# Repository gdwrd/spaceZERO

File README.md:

# spaceZERO
spaceZERO - A 48-key ortholinear keyboard

README.md will be updated soon

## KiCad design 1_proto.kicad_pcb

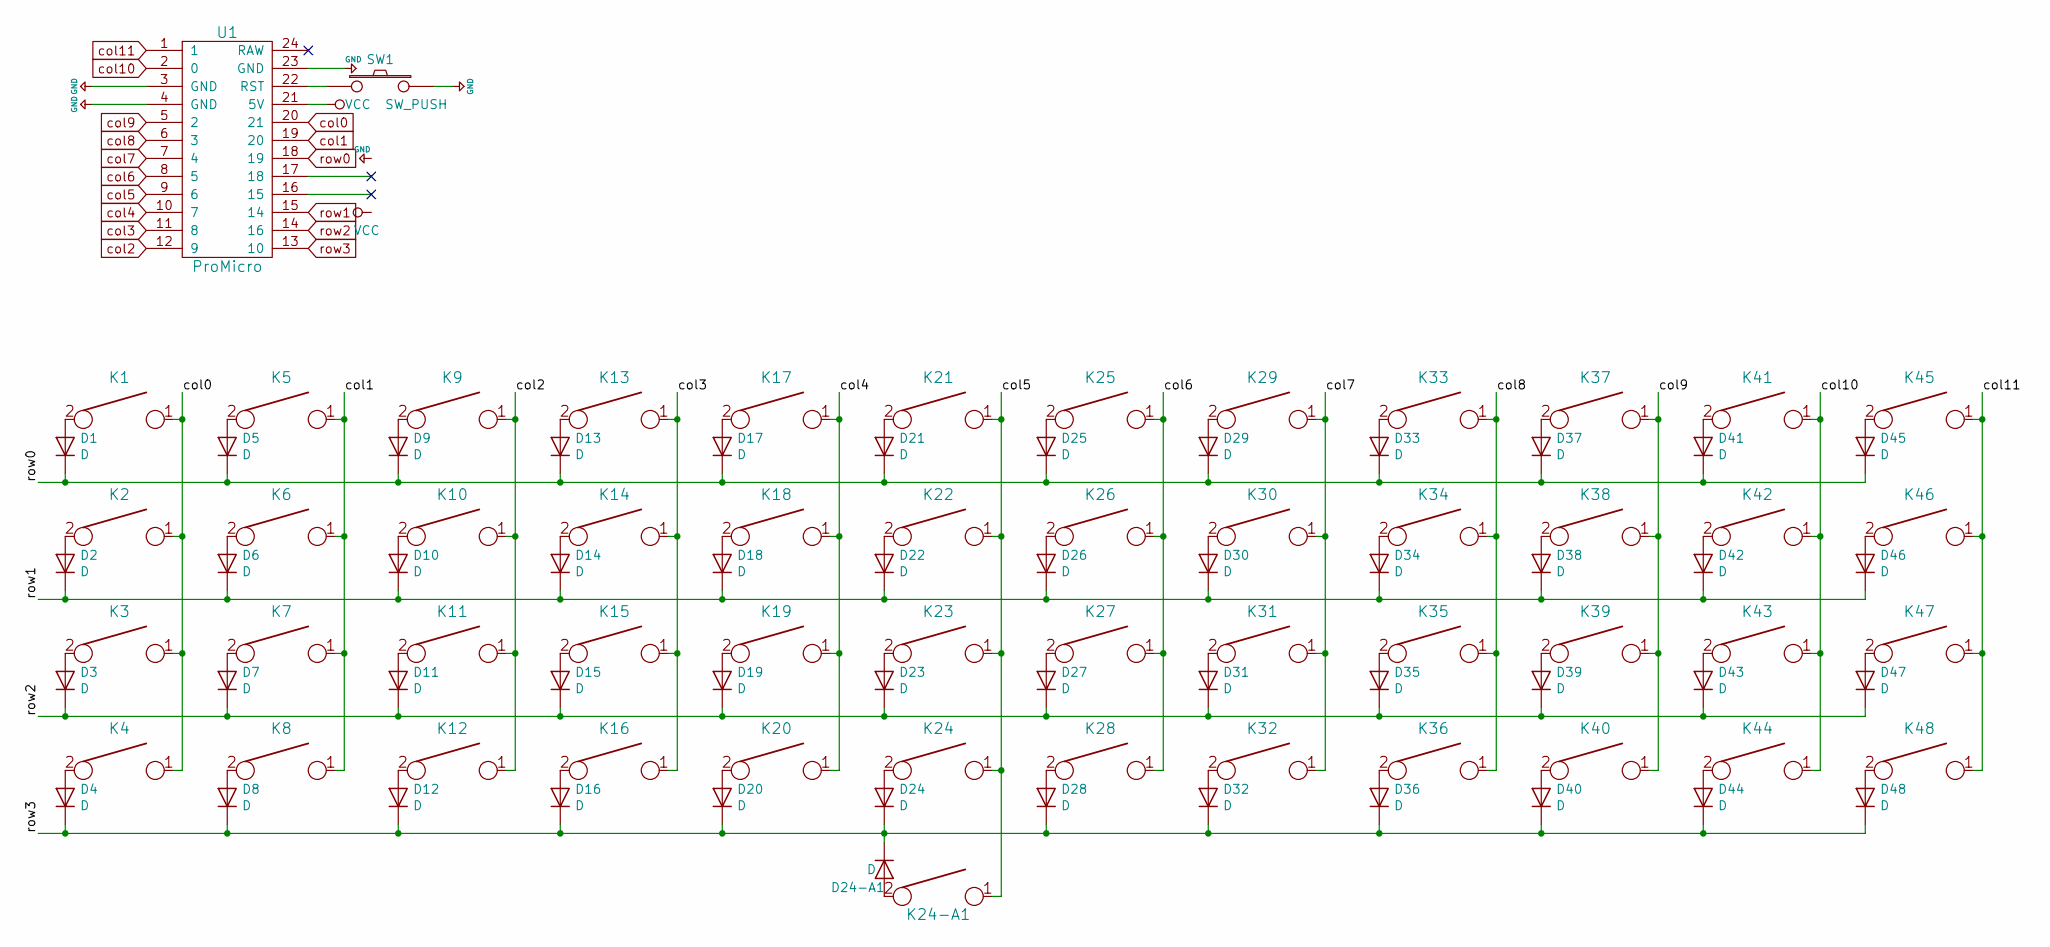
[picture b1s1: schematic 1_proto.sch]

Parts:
D1, D2, D3, D4, D5, D6, D7, D8, D9, D10, D11, D12, D13, D14, D15, D16, D17, D18, D19, D20, D21, D22, D23, D24, D24-A1, D25, D26, D27, D28, D29, D30, D31, D32, D33, D34, D35, D36, D37, D38, D39, D40, D41, D42, D43, D44, D45, D46, D47, D48: D; D_SOD123_axial
K1, K2, K3, K4, K5, K6, K7, K8, K9, K10, K11, K12, K13, K14, K15, K16, K17, K18, K19, K20, K21, K22, K23, K24, K24-A1, K25, K26, K27, K28, K29, K30, K31, K32, K33, K34, K35, K36, K37, K38, K39, K40, K41, K42, K43, K44, K45, K46, K47, K48: KEYSW; Mx_Alps_100
SW1: SW_PUSH; SW_PUSH_6mm
U1: ProMicro; Pro_Micro

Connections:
+5V: SW1.2, U1.3 (GND), U1.4 (GND), U1.23 (GND)
unnamed: D1.2 (A), K1.2
unnamed: D2.2 (A), K2.2
unnamed: D3.2 (A), K3.2
unnamed: D4.2 (A), K4.2
unnamed: D5.2 (A), K5.2
unnamed: D6.2 (A), K6.2
unnamed: D7.2 (A), K7.2
unnamed: D8.2 (A), K8.2
unnamed: D9.2 (A), K9.2
unnamed: D10.2 (A), K10.2
unnamed: D11.2 (A), K11.2
unnamed: D12.2 (A), K12.2
unnamed: D13.2 (A), K13.2
unnamed: D14.2 (A), K14.2
unnamed: D15.2 (A), K15.2
unnamed: D16.2 (A), K16.2
unnamed: D17.2 (A), K17.2
unnamed: D18.2 (A), K18.2
unnamed: D19.2 (A), K19.2
unnamed: D20.2 (A), K20.2
unnamed: D21.2 (A), K21.2
unnamed: D22.2 (A), K22.2
unnamed: D23.2 (A), K23.2
unnamed: D24-A1.2 (A), K24-A1.2
unnamed: D24.2 (A), K24.2
unnamed: D25.2 (A), K25.2
unnamed: D26.2 (A), K26.2
unnamed: D27.2 (A), K27.2
unnamed: D28.2 (A), K28.2
unnamed: D29.2 (A), K29.2
unnamed: D30.2 (A), K30.2
unnamed: D31.2 (A), K31.2
unnamed: D32.2 (A), K32.2
unnamed: D33.2 (A), K33.2
unnamed: D34.2 (A), K34.2
unnamed: D35.2 (A), K35.2
unnamed: D36.2 (A), K36.2
unnamed: D37.2 (A), K37.2
unnamed: D38.2 (A), K38.2
unnamed: D39.2 (A), K39.2
unnamed: D40.2 (A), K40.2
unnamed: D41.2 (A), K41.2
unnamed: D42.2 (A), K42.2
unnamed: D43.2 (A), K43.2
unnamed: D44.2 (A), K44.2
unnamed: D45.2 (A), K45.2
unnamed: D46.2 (A), K46.2
unnamed: D47.2 (A), K47.2
unnamed: D48.2 (A), K48.2
unnamed: SW1.1, U1.22 (RST)
VCC: U1.21 (5V)
col0: K1.1, K2.1, K3.1, K4.1, U1.20 (21)
col1: K5.1, K6.1, K7.1, K8.1, U1.19 (20)
col2: K9.1, K10.1, K11.1, K12.1, U1.12 (9)
col3: K13.1, K14.1, K15.1, K16.1, U1.11 (8)
col4: K17.1, K18.1, K19.1, K20.1, U1.10 (7)
col5: K21.1, K22.1, K23.1, K24.1, K24-A1.1, U1.9 (6)
col6: K25.1, K26.1, K27.1, K28.1, U1.8 (5)
col7: K29.1, K30.1, K31.1, K32.1, U1.7 (4)
col8: K33.1, K34.1, K35.1, K36.1, U1.6 (3)
col9: K37.1, K38.1, K39.1, K40.1, U1.5 (2)
col10: K41.1, K42.1, K43.1, K44.1, U1.2 (0)
col11: K45.1, K46.1, K47.1, K48.1, U1.1
row0: D1.1 (K), D5.1 (K), D9.1 (K), D13.1 (K), D17.1 (K), D21.1 (K), D25.1 (K), D29.1 (K), D33.1 (K), D37.1 (K), D41.1 (K), D45.1 (K), U1.18 (19)
row1: D2.1 (K), D6.1 (K), D10.1 (K), D14.1 (K), D18.1 (K), D22.1 (K), D26.1 (K), D30.1 (K), D34.1 (K), D38.1 (K), D42.1 (K), D46.1 (K), U1.15 (14)
row2: D3.1 (K), D7.1 (K), D11.1 (K), D15.1 (K), D19.1 (K), D23.1 (K), D27.1 (K), D31.1 (K), D35.1 (K), D39.1 (K), D43.1 (K), D47.1 (K), U1.14 (16)
row3: D4.1 (K), D8.1 (K), D12.1 (K), D16.1 (K), D20.1 (K), D24.1 (K), D24-A1.1 (K), D28.1 (K), D32.1 (K), D36.1 (K), D40.1 (K), D44.1 (K), D48.1 (K), U1.13 (10)

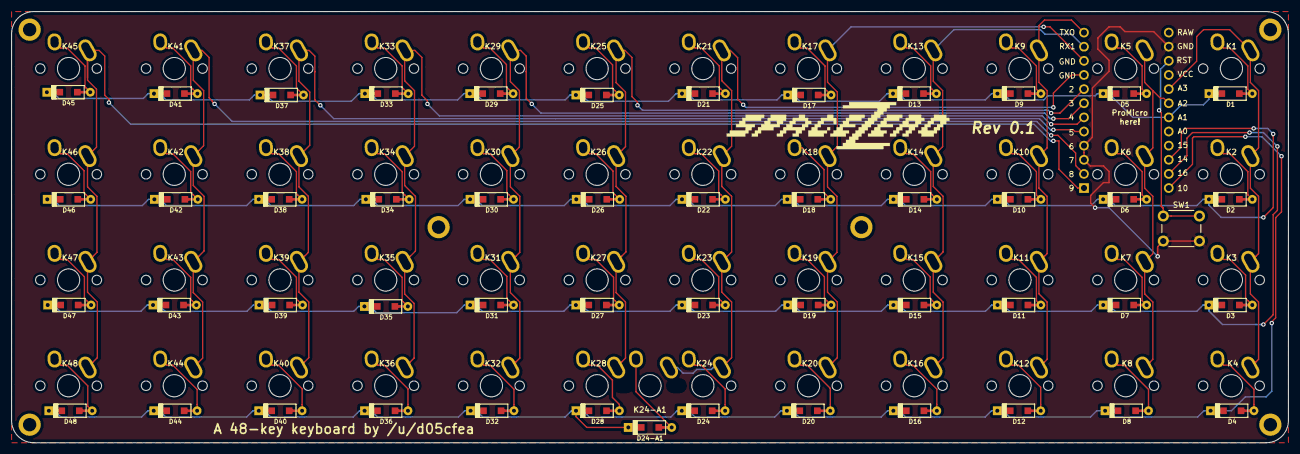
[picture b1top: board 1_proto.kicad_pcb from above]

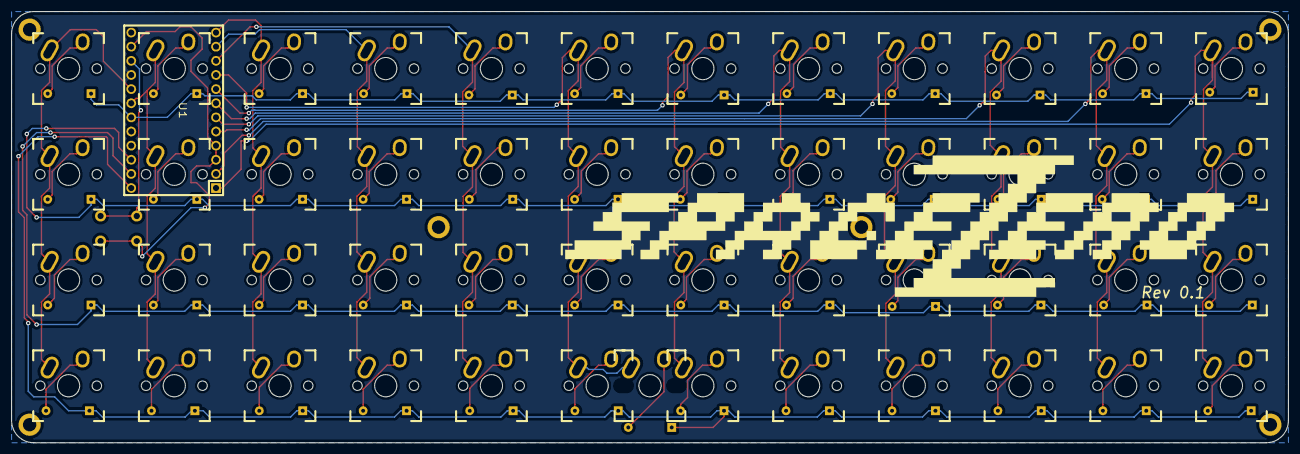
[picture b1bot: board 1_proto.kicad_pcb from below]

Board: 2 copper layers, 229.5 x 77.5 mm, 100 parts (50 on the bottom side), 67 nets.

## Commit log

2019-03-10 Rev 0.1
2019-03-11 added 2u space key support & minor changes
2019-03-11 release SpaceZERO Rev 0.1
2019-03-14 added cases stl files
